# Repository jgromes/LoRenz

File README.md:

# LoRenz

## Arduino shield/module to allow easy use of the LoRa communication modules

---

## Work in progress warning
This shield is still early in developement. The shield, module or breakout layouts might be changed at any moment! Watch this repo for progress updates. To get notifications about every commit, use the following link to set up an RSS feed reader: https://github.com/jgromes/LoRenz/commits/master.atom.

---

### This is not the library you are looking for!
If you're looking for Arduino library to use with these modules, it has its own repository: [https://github.com/jgromes/LoRaLib](https://github.com/jgromes/LoRaLib)

---

DISCLAIMER: All schematic and board files are provided 'AS IS'. see `license.txt` for details.

The following is a listing of all the files in the `eagle` folder:

* `shield`

  This will most likely be the starting point of your experiments with LoRa. The shield is compatible with Arduino R3 pinout and has many ways to make your life easier. The main features include:
  
  * Dedicated 3.3V linear regulator to provide more than enough power for the LoRa module.
  * Arduino UNO and Mega compatibility.
  * On-board prototyping area with separate power rails.
  * Coaxial connector on the breakout board for connecting antenna.
  * NSS jumper to allow for LoRenz shield stacking.
  * The shield has a place for LED that will light up when there are data being transferred to/from the LoRa module. To enable this feature, short the EN pads with solder.
  
  Please note that to use this shield, you will need to have a breakout board to mount the LoRa module.
  IMPORTANT: There are several incompatible types of these modules being sold, make sure that your module matches your breakout board!
  
  <b>Arduino UNO setup:</b>
  
  To use LoRenz shield with Arduino UNO, short all the jumpers on U/M pin header (bright red in the picture below). You will also have to short one of the pin pairs on NSS pin header. The NSS pin header allows you to stack up to four LoRenz shields on one Arduino by shorting different pin pair on each shield. If you will only be using one LoRenz shield, I suggest using the pin 7, since that is the default library setting. If you want to stack multiple LoRenz shields, each of them must have a different pin pair shorted. In that case, you will also have to provide the selected pin numbers to LoRaLib. See the library reference for details.

  <b>Arduino Mega setup:</b>
  
  To use LoRenz shield with Arduino Mega, remove all the shorting jumpers from U/M pin header. Arduino Mega has the SPI located on pins 50-53, connect the shield to these pins as per the following image. The NSS selection is the same as with Arduino UNO.

* `breakout_green`

  This breakout board matches the following LoRa module:

  These seem to be fairly common, however, there are several slightly different pinouts. Prior to any soldering, make sure that the module pinout matches the pin description on the breakout board!

* `breakout_blue`

  This breakout board matches the following LoRa module:

  The amount of these modules on the market seems to be declining lately, but it's still possible to buy them. Again, there are multiple different pinouts.

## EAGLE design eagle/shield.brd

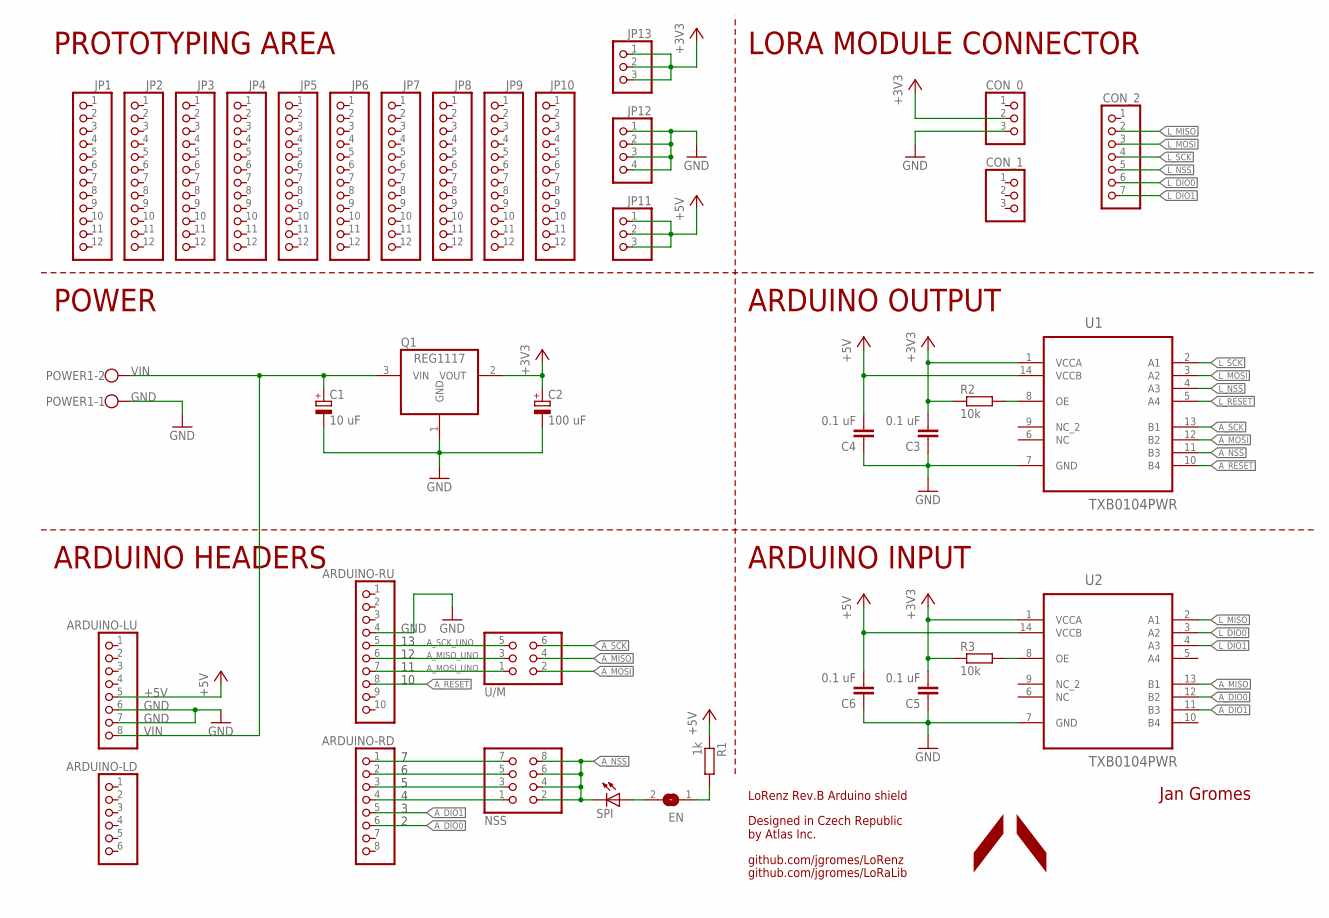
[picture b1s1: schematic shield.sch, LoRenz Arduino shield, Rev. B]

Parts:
ARDUINO-LD: PINHD-1X6; 1X06
ARDUINO-LU: PINHD-1X8; 1X08
ARDUINO-RD: PINHD-1X8; 1X08
ARDUINO-RU: PINHD-1X10; 1X10
C1: 10 uF; SMC_A
C2: 100 uF; SMC_B
C3, C4, C5, C6: 0.1 uF; C0603
CON_0, CON_1: PINHD-1X3; 1X03
CON_2: PINHD-1X7; 1X07
EN: SJ
JP1, JP2, JP3, JP4, JP5, JP6, JP7, JP8, JP9, JP10: PINHD-1X12-CB; 1X12-CB
JP11, JP13: PINHD-1X3CB; 1X03-CLEANBIG
JP12: PINHD-1X4; 1X04-CLEANBIG
NSS: PINHD-2X4; 2X04
POWER1: W237-102
Q1: REG1117; SOT223
R1: 1k; R0603
R2, R3: 10k; R0603
SPI: LEDSML0603; SML0603
U1, U2: TXB0104PWR; SOP65P640X120-14N
U/M: PINHD-2X3; 2X03

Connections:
+3V3: C2.+, C3.2, C5.2, CON_0.2, JP13.1, JP13.2, JP13.3, Q1.2 (VOUT), R2.1, R3.1, U1.1 (VCCA), U2.1 (VCCA)
+5V: ARDUINO-LU.5, C4.2, C6.2, JP11.1, JP11.2, JP11.3, R1.1, U1.14 (VCCB), U2.14 (VCCB)
A_DIO0: ARDUINO-RD.6, U2.12 (B2)
A_DIO1: ARDUINO-RD.5, U2.11 (B3)
A_MISO: U2.13 (B1), U/M.4
A_MISO_UNO: ARDUINO-RU.6, U/M.3
A_MOSI: U1.12 (B2), U/M.2
A_MOSI_UNO: ARDUINO-RU.7, U/M.1
A_NSS: NSS.2, NSS.4, NSS.6, NSS.8, SPI.C, U1.11 (B3)
A_RESET: ARDUINO-RU.8, U1.10 (B4)
A_SCK: U1.13 (B1), U/M.6
A_SCK_UNO: ARDUINO-RU.5, U/M.5
GND: ARDUINO-LU.6, ARDUINO-LU.7, ARDUINO-RU.4, C1.-, C2.-, C3.1, C4.1, C5.1, C6.1, CON_0.3, JP12.1, JP12.2, JP12.3, JP12.4, POWER1.1, Q1.1 (GND), U1.7 (GND), U2.7 (GND)
L_DIO0: CON_2.6, U2.3 (A2)
L_DIO1: CON_2.7, U2.4 (A3)
L_MISO: CON_2.2, U2.2 (A1)
L_MOSI: CON_2.3, U1.3 (A2)
L_NSS: CON_2.5, U1.4 (A3)
L_RESET: U1.5 (A4)
L_SCK: CON_2.4, U1.2 (A1)
unnamed: ARDUINO-RD.1, NSS.7
unnamed: EN.2, SPI.A
unnamed: ARDUINO-RD.2, NSS.5
unnamed: ARDUINO-RD.3, NSS.3
unnamed: ARDUINO-RD.4, NSS.1
unnamed: EN.1, R1.2
unnamed: R2.2, U1.8 (OE)
unnamed: R3.2, U2.8 (OE)
VIN: ARDUINO-LU.8, C1.+, POWER1.2, Q1.3 (VIN)

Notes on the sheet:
LoRenz Rev.B Arduino shield
Designed in Czech Republic by Atlas Inc.
github.com/jgromes/LoRenz
github.com/jgromes/LoRaLib
Jan Gromes
C:/Users/Honza/Desktop/ATLAS/atlas_logo_notext_gs.bmp
PROTOTYPING AREA
LORA MODULE CONNECTOR
ARDUINO INPUT
POWER
ARDUINO OUTPUT
ARDUINO HEADERS

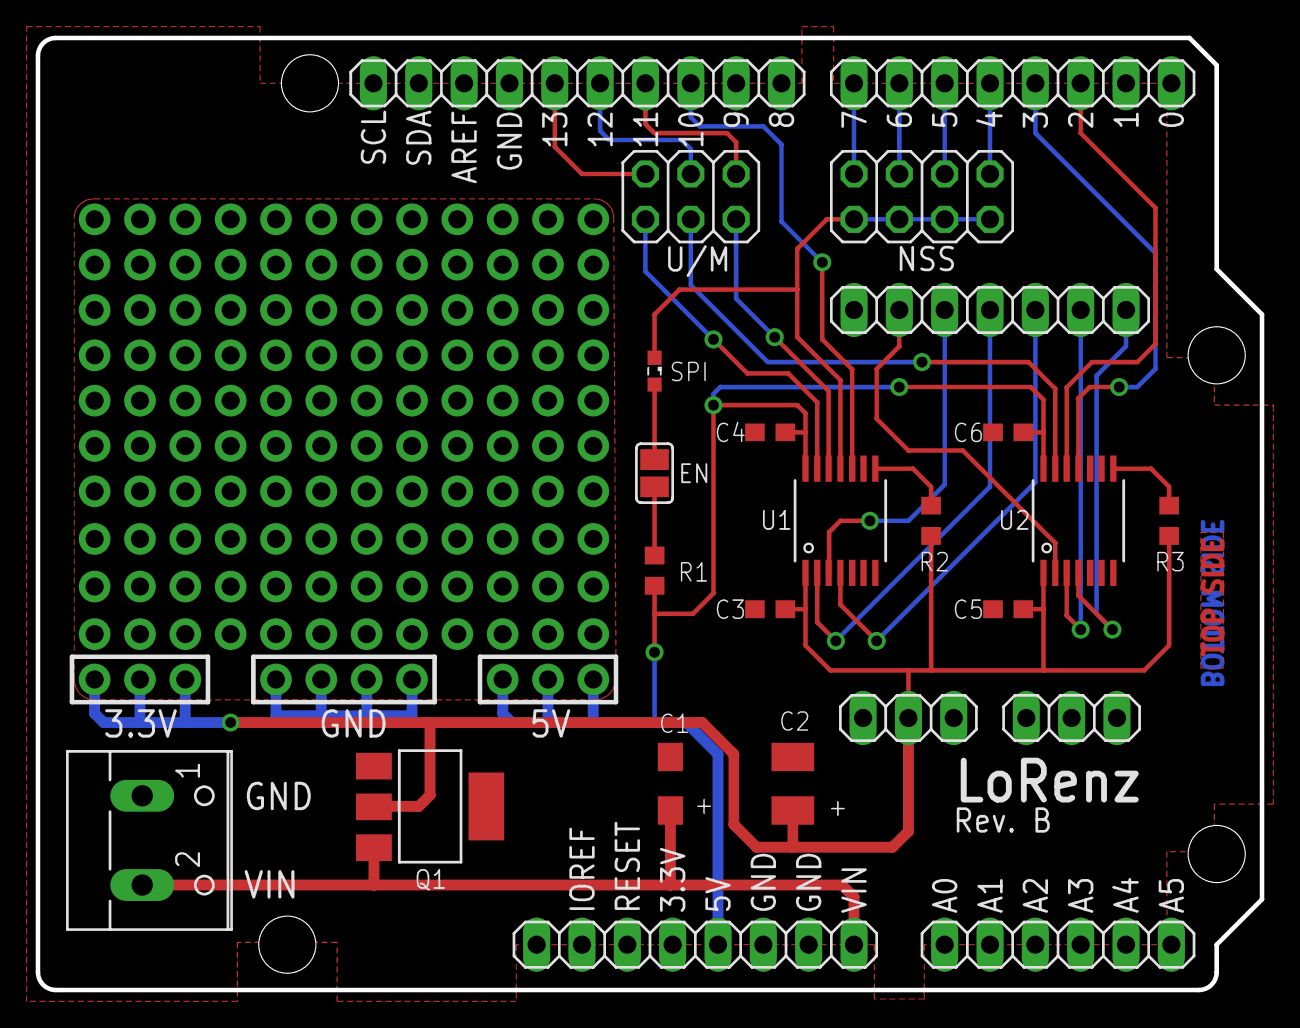
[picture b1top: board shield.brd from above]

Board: 2 copper layers, 68.6 x 53.3 mm, 37 parts (0 on the bottom side), 28 nets.

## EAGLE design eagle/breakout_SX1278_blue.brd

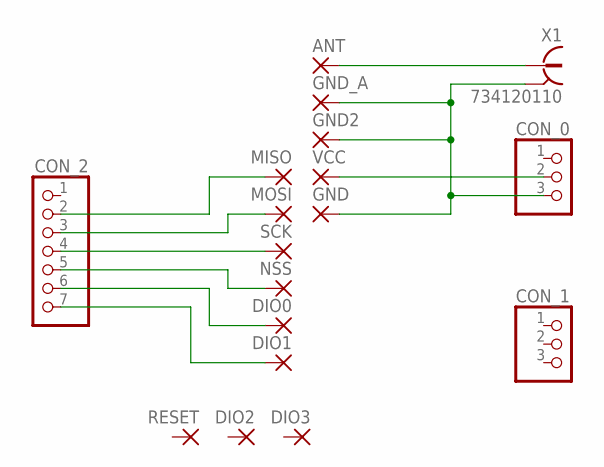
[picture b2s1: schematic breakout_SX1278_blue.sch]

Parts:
ANT: SMD1; SMD0,65-1,27
CON_0, CON_1: PINHD-1X3; 1X03
CON_2: PINHD-1X7; 1X07
DIO0, DIO1, DIO2, DIO3: SMD1; SMD0,65-1,27
GND, GND2: SMD1; SMD0,65-1,27
GND_A: SMD1; SMD0,65-1,27
MISO: SMD1; SMD0,65-1,27
MOSI: SMD1; SMD0,65-1,27
NSS: SMD1; SMD0,65-1,27
RESET: SMD1; SMD0,65-1,27
SCK: SMD1; SMD0,65-1,27
VCC: SMD1; SMD0,65-1,27
X1: 734120110

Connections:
3.3V: CON_0.2, VCC.1; also elsewhere on the board
ANT: ANT.1, X1.1
DIO0: CON_2.6, DIO0.1
DIO1: CON_2.7, DIO1.1
GND: CON_0.3, GND.1, GND2.1, GND_A.1, X1.S@1 (2), X1.S@2 (2), X1.S@3 (2)
MISO: CON_2.2, MISO.1
MOSI: CON_2.3, MOSI.1
NSS: CON_2.5, NSS.1
SCK: CON_2.4, SCK.1

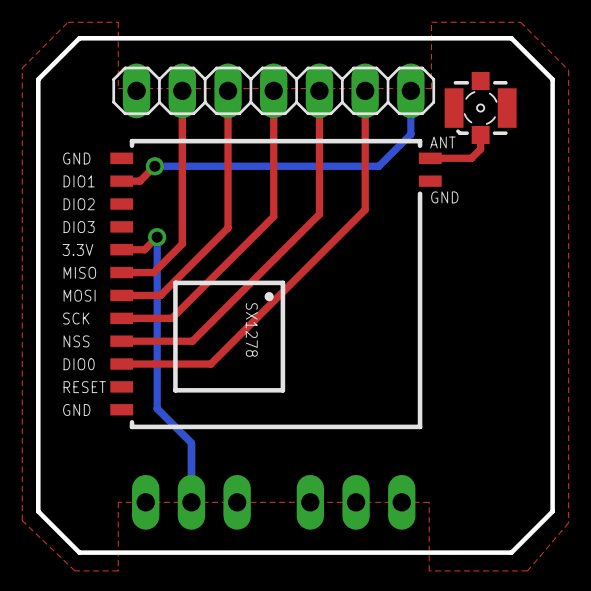
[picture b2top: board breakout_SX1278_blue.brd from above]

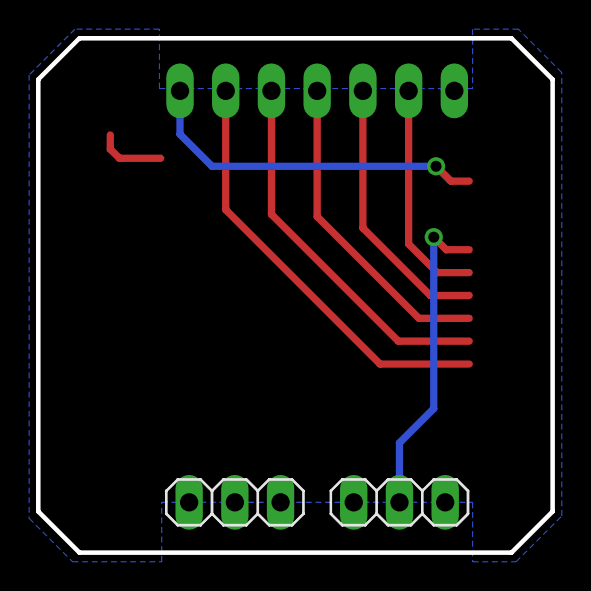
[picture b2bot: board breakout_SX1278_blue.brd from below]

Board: 2 copper layers, 28.6 x 28.6 mm, 18 parts (2 on the bottom side), 9 nets.

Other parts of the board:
3.3V: SMD0,65-1,27

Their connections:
3.3V: 3.3V.1; also elsewhere on the board

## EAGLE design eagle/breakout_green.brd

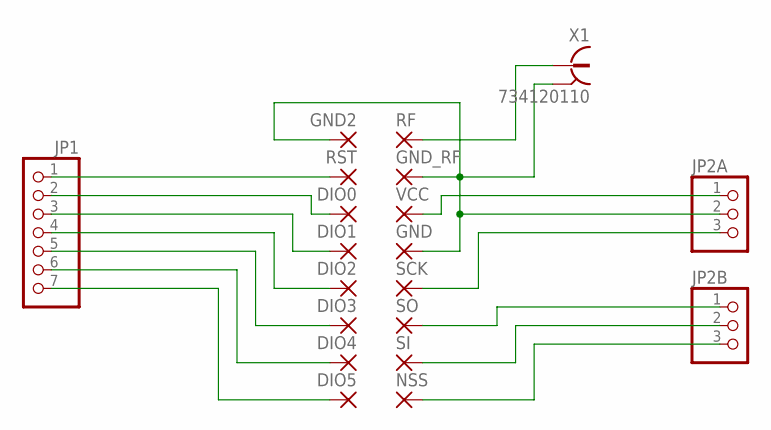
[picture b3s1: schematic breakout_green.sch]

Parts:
DIO0, DIO1, DIO2, DIO3, DIO4, DIO5: SMD2; SMD1,27-2,54
GND, GND2: SMD2; SMD1,27-2,54
GND_RF: SMD2; SMD1,27-2,54
JP1: PINHD-1X7; 1X07
JP2A, JP2B: PINHD-1X3; 1X03
NSS: SMD2; SMD1,27-2,54
RF: SMD2; SMD1,27-2,54
RST: SMD2; SMD1,27-2,54
SCK: SMD2; SMD1,27-2,54
SI: SMD2; SMD1,27-2,54
SO: SMD2; SMD1,27-2,54
VCC: SMD2; SMD1,27-2,54
X1: 734120110

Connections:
3.3V: JP2A.1, VCC.1
ANT: RF.1, X1.1
DIO0: DIO0.1, JP1.2
DIO1: DIO1.1, JP1.3
DIO2: DIO2.1, JP1.4
DIO3: DIO3.1, JP1.5
DIO4: DIO4.1, JP1.6
DIO5: DIO5.1, JP1.7
GND: GND.1, GND2.1, GND_RF.1, JP2A.2, X1.S@1 (2), X1.S@2 (2), X1.S@3 (2)
MISO: JP2B.1, SO.1
MOSI: JP2B.2, SI.1
NSS: JP2B.3, NSS.1
RESET: JP1.1, RST.1
SCK: JP2A.3, SCK.1

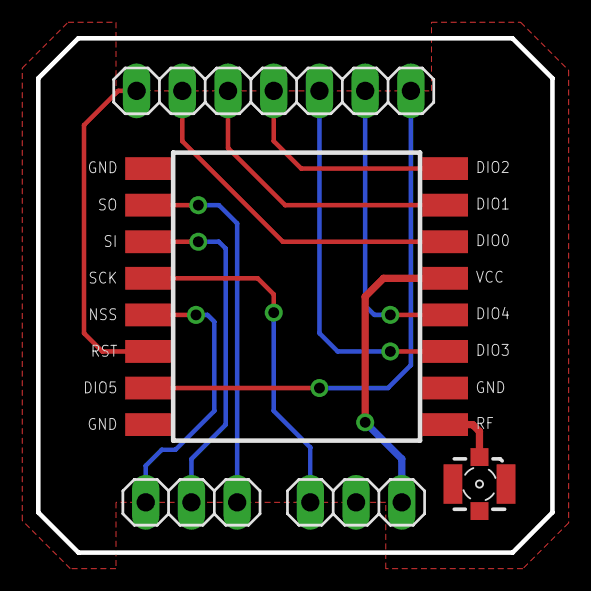
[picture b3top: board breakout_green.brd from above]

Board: 2 copper layers, 28.6 x 28.6 mm, 20 parts (0 on the bottom side), 14 nets.

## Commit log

2017-01-29 Rename LICENSE to license.txt
2017-03-17 Added shield and breakout boards Eagle files
2017-03-20 Fixed LoRa module pad spacing
2017-03-20 Added Readme
2017-04-01 Shield layout update
    Added two separate TXB0104 instead of one TXB0108 (signal direction issues), added EN solder jumper for LED, removed battery level measurement, increased the protoyping area size, general layout chan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
2017-04-01 Shield and breakout layout update
    Added a gap to the pin headers on LoRa breakout board and the shield to enforce breakout orientation.
2017-04-02 Rename breakout_blue.brd to breakout_SX1278_blue.brd
2017-04-02 Rename breakout_blue.sch to breakout_SX1278_blue.sch
2017-04-02 Rename breakout_green.brd to breakout_SX1278_green.brd
2017-04-02 Rename breakout_green.sch to breakout_SX1278_green.sch
2017-04-02 Added SX1278 outline as an orientation marker
2017-04-05 Orientation marker fix
2017-04-15 Create doc
2017-04-15 Added module photos
2017-04-22 Add Fritzing part and SVG files
2017-05-04 Added shield image
2017-05-05 Module layout update
2017-05-06 Added README images
2017-05-06 Changed package of C2
2017-05-08 RSS link fix
2017-05-11 Breakout dimensions fix
2017-05-11 Major layout update, read details
    The layouts of shield and all breakout boards were changed to match the new multiprotocol standard.
    IMPORTANT: The new shield is NOT compatible with the old breakout boards!
2017-06-12 Fixed power connector orientation
2017-06-20 Release 1.0
2017-06-21 Updated docs to match current release
2017-06-21 Updated gitignore
2017-06-24 Added shield assembly guide
